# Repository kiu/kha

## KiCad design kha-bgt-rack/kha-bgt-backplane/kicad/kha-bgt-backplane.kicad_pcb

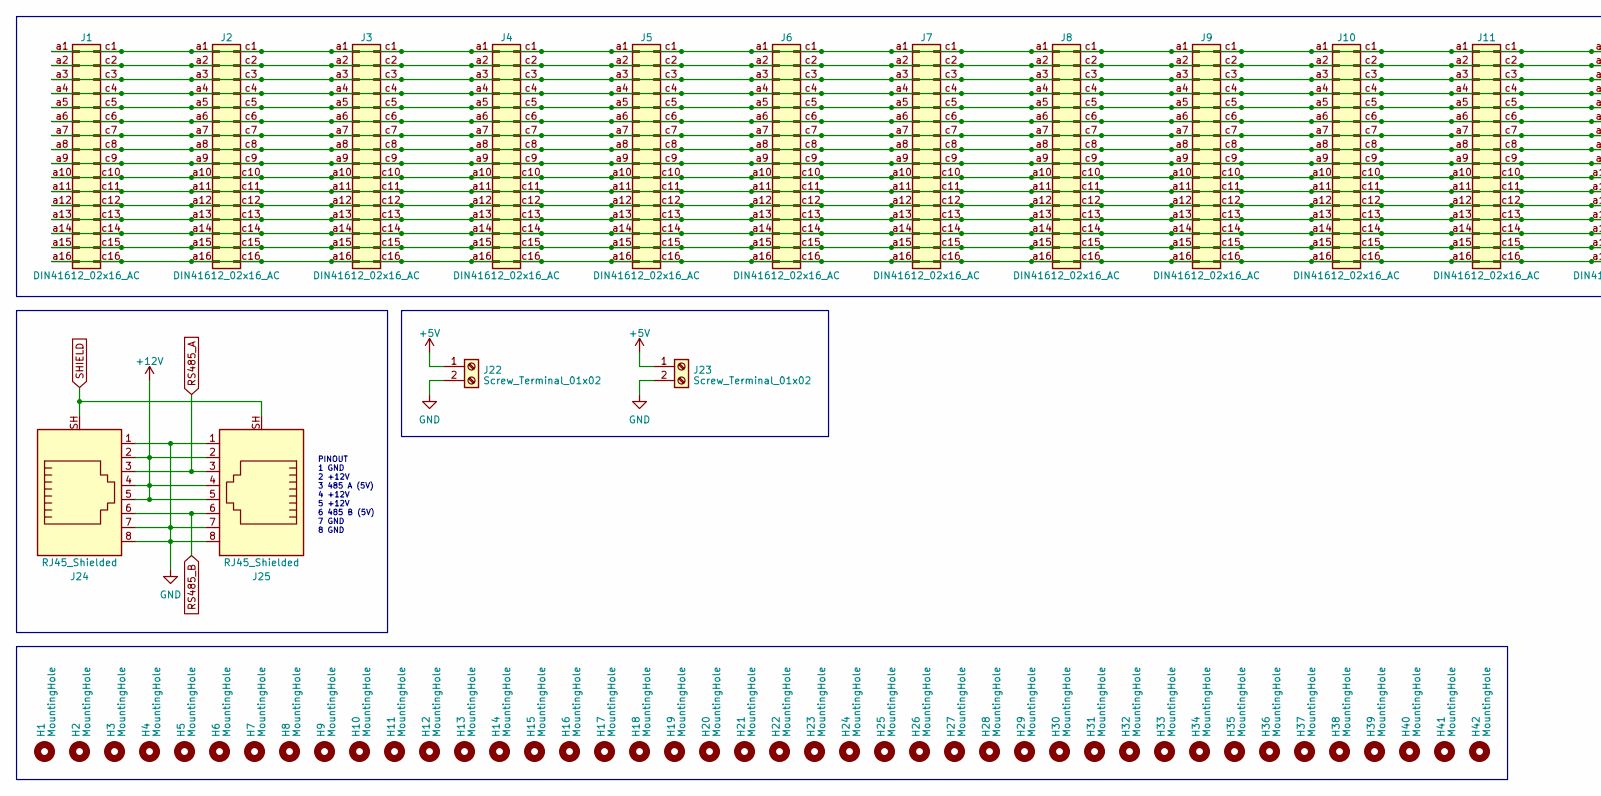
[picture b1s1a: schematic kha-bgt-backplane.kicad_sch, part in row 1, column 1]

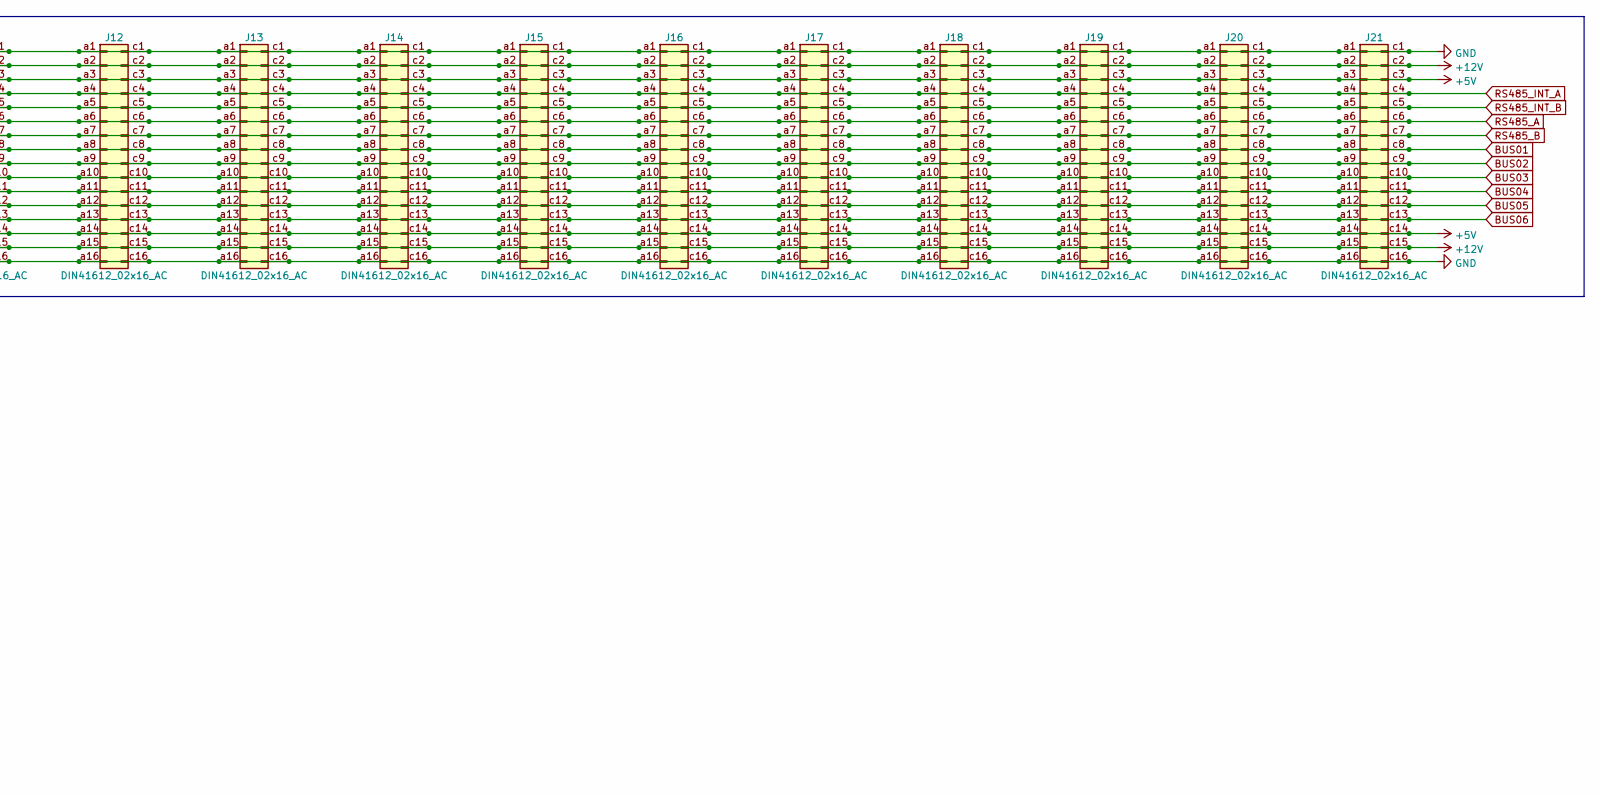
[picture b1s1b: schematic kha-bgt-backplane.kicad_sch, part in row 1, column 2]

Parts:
H1, H2, H3, H4, H5, H6, H7, H8, H9, H10, H11, H12, H13, H14, H15, H16, H17, H18, H19, H20, H21, H22, H23, H24, H25, H26, H27, H28, H29, H30, H31, H32, H33, H34, H35, H36, H37, H38, H39, H40, H41, H42: MountingHole; MountingHole_2.5mm
J1, J2, J3, J4, J5, J6, J7, J8, J9, J10, J11, J12, J13, J14, J15, J16, J17, J18, J19, J20, J21: DIN41612_02x16_AC; DIN41612_C2_2x16_Female_Vertical_THT
J22, J23: Screw_Terminal_01x02; TerminalBlock_RND_205-00232_1x02_P5.08mm_Horizontal
J24, J25: RJ45_Shielded; GDLX-S-88K

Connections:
+5V: J1.a3, J1.a14, J1.c3, J1.c14, J2.a3, J2.a14, J2.c3, J2.c14, J3.a3, J3.a14, J3.c3, J3.c14, J4.a3, J4.a14, J4.c3, J4.c14, J5.a3, J5.a14, J5.c3, J5.c14, J6.a3, J6.a14, J6.c3, J6.c14, J7.a3, J7.a14, J7.c3, J7.c14, J8.a3, J8.a14, J8.c3, J8.c14, J9.a3, J9.a14, J9.c3, J9.c14, J10.a3, J10.a14, J10.c3, J10.c14, J11.a3, J11.a14, J11.c3, J11.c14, J12.a3, J12.a14, J12.c3, J12.c14, J13.a3, J13.a14, J13.c3, J13.c14, J14.a3, J14.a14, J14.c3, J14.c14, J15.a3, J15.a14, J15.c3, J15.c14, J16.a3, J16.a14, J16.c3, J16.c14, J17.a3, J17.a14, J17.c3, J17.c14, J18.a3, J18.a14, J18.c3, J18.c14, J19.a3, J19.a14, J19.c3, J19.c14, J20.a3, J20.a14, J20.c3, J20.c14, J21.a3, J21.a14, J21.c3, J21.c14, J22.1, J23.1
+12V: J1.a2, J1.a15, J1.c2, J1.c15, J2.a2, J2.a15, J2.c2, J2.c15, J3.a2, J3.a15, J3.c2, J3.c15, J4.a2, J4.a15, J4.c2, J4.c15, J5.a2, J5.a15, J5.c2, J5.c15, J6.a2, J6.a15, J6.c2, J6.c15, J7.a2, J7.a15, J7.c2, J7.c15, J8.a2, J8.a15, J8.c2, J8.c15, J9.a2, J9.a15, J9.c2, J9.c15, J10.a2, J10.a15, J10.c2, J10.c15, J11.a2, J11.a15, J11.c2, J11.c15, J12.a2, J12.a15, J12.c2, J12.c15, J13.a2, J13.a15, J13.c2, J13.c15, J14.a2, J14.a15, J14.c2, J14.c15, J15.a2, J15.a15, J15.c2, J15.c15, J16.a2, J16.a15, J16.c2, J16.c15, J17.a2, J17.a15, J17.c2, J17.c15, J18.a2, J18.a15, J18.c2, J18.c15, J19.a2, J19.a15, J19.c2, J19.c15, J20.a2, J20.a15, J20.c2, J20.c15, J21.a2, J21.a15, J21.c2, J21.c15, J24.2, J24.4, J24.5, J25.2, J25.4, J25.5
BUS01: J1.a8, J1.c8, J2.a8, J2.c8, J3.a8, J3.c8, J4.a8, J4.c8, J5.a8, J5.c8, J6.a8, J6.c8, J7.a8, J7.c8, J8.a8, J8.c8, J9.a8, J9.c8, J10.a8, J10.c8, J11.a8, J11.c8, J12.a8, J12.c8, J13.a8, J13.c8, J14.a8, J14.c8, J15.a8, J15.c8, J16.a8, J16.c8, J17.a8, J17.c8, J18.a8, J18.c8, J19.a8, J19.c8, J20.a8, J20.c8, J21.a8, J21.c8
BUS02: J1.a9, J1.c9, J2.a9, J2.c9, J3.a9, J3.c9, J4.a9, J4.c9, J5.a9, J5.c9, J6.a9, J6.c9, J7.a9, J7.c9, J8.a9, J8.c9, J9.a9, J9.c9, J10.a9, J10.c9, J11.a9, J11.c9, J12.a9, J12.c9, J13.a9, J13.c9, J14.a9, J14.c9, J15.a9, J15.c9, J16.a9, J16.c9, J17.a9, J17.c9, J18.a9, J18.c9, J19.a9, J19.c9, J20.a9, J20.c9, J21.a9, J21.c9
BUS03: J1.a10, J1.c10, J2.a10, J2.c10, J3.a10, J3.c10, J4.a10, J4.c10, J5.a10, J5.c10, J6.a10, J6.c10, J7.a10, J7.c10, J8.a10, J8.c10, J9.a10, J9.c10, J10.a10, J10.c10, J11.a10, J11.c10, J12.a10, J12.c10, J13.a10, J13.c10, J14.a10, J14.c10, J15.a10, J15.c10, J16.a10, J16.c10, J17.a10, J17.c10, J18.a10, J18.c10, J19.a10, J19.c10, J20.a10, J20.c10, J21.a10, J21.c10
BUS04: J1.a11, J1.c11, J2.a11, J2.c11, J3.a11, J3.c11, J4.a11, J4.c11, J5.a11, J5.c11, J6.a11, J6.c11, J7.a11, J7.c11, J8.a11, J8.c11, J9.a11, J9.c11, J10.a11, J10.c11, J11.a11, J11.c11, J12.a11, J12.c11, J13.a11, J13.c11, J14.a11, J14.c11, J15.a11, J15.c11, J16.a11, J16.c11, J17.a11, J17.c11, J18.a11, J18.c11, J19.a11, J19.c11, J20.a11, J20.c11, J21.a11, J21.c11
BUS05: J1.a12, J1.c12, J2.a12, J2.c12, J3.a12, J3.c12, J4.a12, J4.c12, J5.a12, J5.c12, J6.a12, J6.c12, J7.a12, J7.c12, J8.a12, J8.c12, J9.a12, J9.c12, J10.a12, J10.c12, J11.a12, J11.c12, J12.a12, J12.c12, J13.a12, J13.c12, J14.a12, J14.c12, J15.a12, J15.c12, J16.a12, J16.c12, J17.a12, J17.c12, J18.a12, J18.c12, J19.a12, J19.c12, J20.a12, J20.c12, J21.a12, J21.c12
BUS06: J1.a13, J1.c13, J2.a13, J2.c13, J3.a13, J3.c13, J4.a13, J4.c13, J5.a13, J5.c13, J6.a13, J6.c13, J7.a13, J7.c13, J8.a13, J8.c13, J9.a13, J9.c13, J10.a13, J10.c13, J11.a13, J11.c13, J12.a13, J12.c13, J13.a13, J13.c13, J14.a13, J14.c13, J15.a13, J15.c13, J16.a13, J16.c13, J17.a13, J17.c13, J18.a13, J18.c13, J19.a13, J19.c13, J20.a13, J20.c13, J21.a13, J21.c13
GND: J1.a1, J1.a16, J1.c1, J1.c16, J2.a1, J2.a16, J2.c1, J2.c16, J3.a1, J3.a16, J3.c1, J3.c16, J4.a1, J4.a16, J4.c1, J4.c16, J5.a1, J5.a16, J5.c1, J5.c16, J6.a1, J6.a16, J6.c1, J6.c16, J7.a1, J7.a16, J7.c1, J7.c16, J8.a1, J8.a16, J8.c1, J8.c16, J9.a1, J9.a16, J9.c1, J9.c16, J10.a1, J10.a16, J10.c1, J10.c16, J11.a1, J11.a16, J11.c1, J11.c16, J12.a1, J12.a16, J12.c1, J12.c16, J13.a1, J13.a16, J13.c1, J13.c16, J14.a1, J14.a16, J14.c1, J14.c16, J15.a1, J15.a16, J15.c1, J15.c16, J16.a1, J16.a16, J16.c1, J16.c16, J17.a1, J17.a16, J17.c1, J17.c16, J18.a1, J18.a16, J18.c1, J18.c16, J19.a1, J19.a16, J19.c1, J19.c16, J20.a1, J20.a16, J20.c1, J20.c16, J21.a1, J21.a16, J21.c1, J21.c16, J22.2, J23.2, J24.1, J24.7, J24.8, J25.1, J25.7, J25.8
RS485_A: J1.a6, J1.c6, J2.a6, J2.c6, J3.a6, J3.c6, J4.a6, J4.c6, J5.a6, J5.c6, J6.a6, J6.c6, J7.a6, J7.c6, J8.a6, J8.c6, J9.a6, J9.c6, J10.a6, J10.c6, J11.a6, J11.c6, J12.a6, J12.c6, J13.a6, J13.c6, J14.a6, J14.c6, J15.a6, J15.c6, J16.a6, J16.c6, J17.a6, J17.c6, J18.a6, J18.c6, J19.a6, J19.c6, J20.a6, J20.c6, J21.a6, J21.c6, J24.3, J25.3
RS485_B: J1.a7, J1.c7, J2.a7, J2.c7, J3.a7, J3.c7, J4.a7, J4.c7, J5.a7, J5.c7, J6.a7, J6.c7, J7.a7, J7.c7, J8.a7, J8.c7, J9.a7, J9.c7, J10.a7, J10.c7, J11.a7, J11.c7, J12.a7, J12.c7, J13.a7, J13.c7, J14.a7, J14.c7, J15.a7, J15.c7, J16.a7, J16.c7, J17.a7, J17.c7, J18.a7, J18.c7, J19.a7, J19.c7, J20.a7, J20.c7, J21.a7, J21.c7, J24.6, J25.6
RS485_INT_A: J1.a4, J1.c4, J2.a4, J2.c4, J3.a4, J3.c4, J4.a4, J4.c4, J5.a4, J5.c4, J6.a4, J6.c4, J7.a4, J7.c4, J8.a4, J8.c4, J9.a4, J9.c4, J10.a4, J10.c4, J11.a4, J11.c4, J12.a4, J12.c4, J13.a4, J13.c4, J14.a4, J14.c4, J15.a4, J15.c4, J16.a4, J16.c4, J17.a4, J17.c4, J18.a4, J18.c4, J19.a4, J19.c4, J20.a4, J20.c4, J21.a4, J21.c4
RS485_INT_B: J1.a5, J1.c5, J2.a5, J2.c5, J3.a5, J3.c5, J4.a5, J4.c5, J5.a5, J5.c5, J6.a5, J6.c5, J7.a5, J7.c5, J8.a5, J8.c5, J9.a5, J9.c5, J10.a5, J10.c5, J11.a5, J11.c5, J12.a5, J12.c5, J13.a5, J13.c5, J14.a5, J14.c5, J15.a5, J15.c5, J16.a5, J16.c5, J17.a5, J17.c5, J18.a5, J18.c5, J19.a5, J19.c5, J20.a5, J20.c5, J21.a5, J21.c5
SHIELD: J24.SH, J25.SH

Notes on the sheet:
PINOUT 1 GND 2 +12V 3 485 A (5V) 4 +12V 5 +12V 6 485 B (5V) 7 GND 8 GND

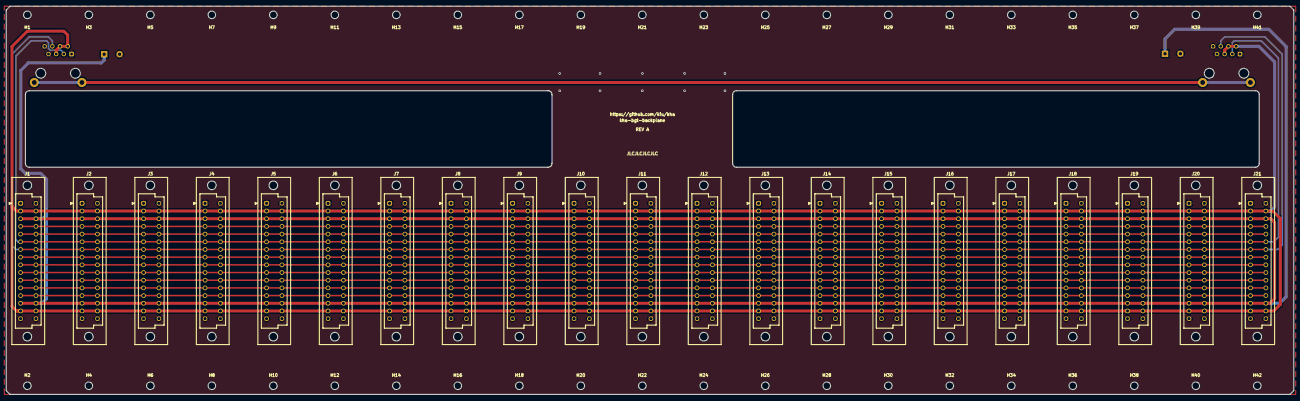
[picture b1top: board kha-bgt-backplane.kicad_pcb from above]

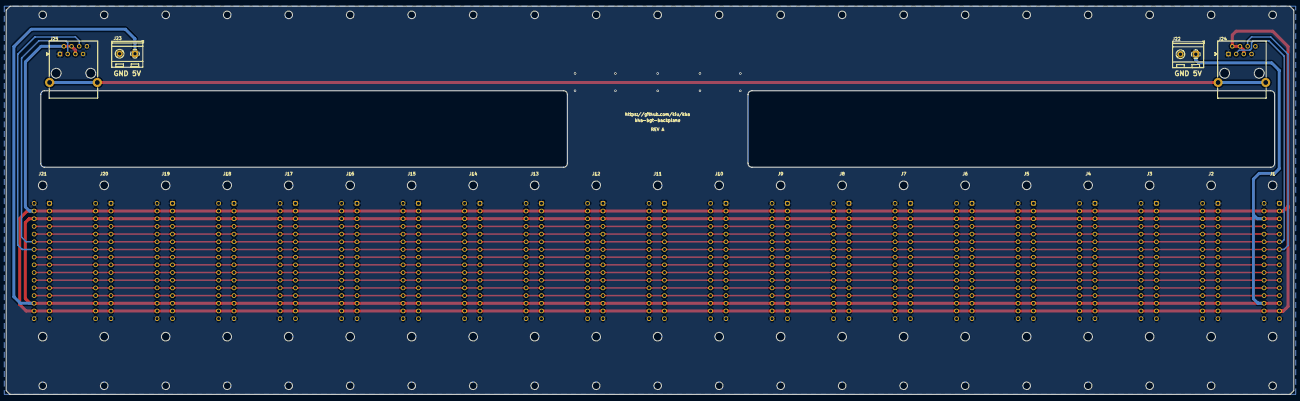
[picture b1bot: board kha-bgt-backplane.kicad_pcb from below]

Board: 2 copper layers, 425.4 x 128.3 mm, 67 parts (4 on the bottom side), 14 nets.

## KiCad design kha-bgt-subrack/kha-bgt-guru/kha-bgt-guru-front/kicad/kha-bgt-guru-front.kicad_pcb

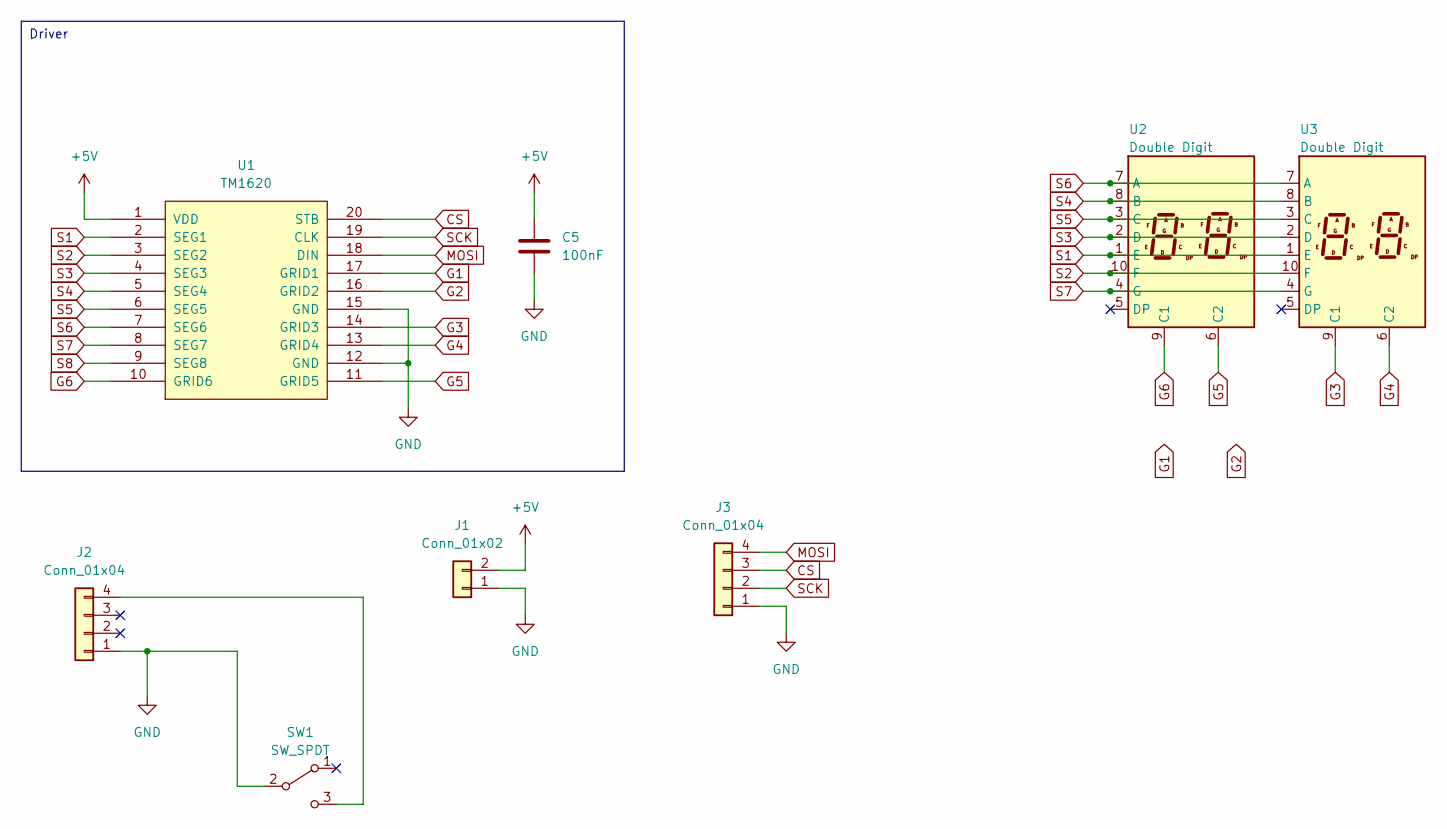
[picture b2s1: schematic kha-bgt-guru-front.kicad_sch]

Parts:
C5: 100nF; C_0805_2012Metric
J1: Conn_01x02; JST_PH_B2B-PH-SM4-TB_1x02-1MP_P2.00mm_Vertical
J2, J3: Conn_01x04; JST_PH_B4B-PH-SM4-TB_1x04-1MP_P2.00mm_Vertical
SW1: SW_SPDT; PB86
U1: TM1620_[C19579]; SOIC-20W_7.5x12.8mm_P1.27mm
U2, U3: Double Digit; SLR028

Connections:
+5V: C5.1, J1.2, U1.1 (VDD)
CS: J3.3, U1.20 (STB)
G1: U1.17 (GRID1)
G2: U1.16 (GRID2)
G3: U1.14 (GRID3), U3.9 (C1)
G4: U1.13 (GRID4), U3.6 (C2)
G5: U1.11 (GRID5), U2.6 (C2)
G6: U1.10 (GRID6), U2.9 (C1)
GND: C5.2, J1.1, J2.1, J3.1, SW1.2 (B), U1.12 (GND), U1.15 (GND)
MOSI: J3.4, U1.18 (DIN)
unnamed: J2.4, SW1.3 (C)
S1: U1.2 (SEG1), U2.1 (E), U3.1 (E)
S2: U1.3 (SEG2), U2.10 (F), U3.10 (F)
S3: U1.4 (SEG3), U2.2 (D), U3.2 (D)
S4: U1.5 (SEG4), U2.8 (B), U3.8 (B)
S5: U1.6 (SEG5), U2.3 (C), U3.3 (C)
S6: U1.7 (SEG6), U2.7 (A), U3.7 (A)
S7: U1.8 (SEG7), U2.4 (G), U3.4 (G)
S8: U1.9 (SEG8)
SCK: J3.2, U1.19 (CLK)

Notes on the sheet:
Driver

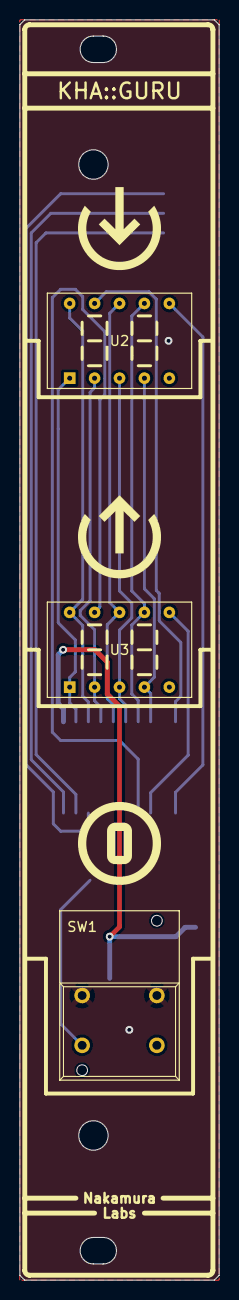
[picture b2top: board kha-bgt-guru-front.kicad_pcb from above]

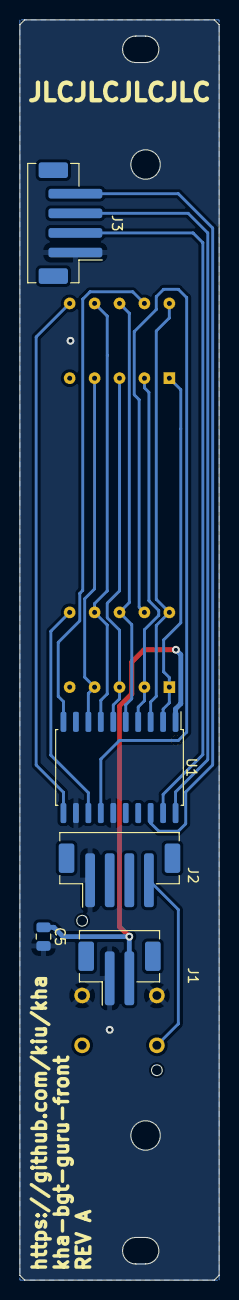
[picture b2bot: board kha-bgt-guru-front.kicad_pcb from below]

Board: 2 copper layers, 20.3 x 128.5 mm, 8 parts (5 on the bottom side), 17 nets.
